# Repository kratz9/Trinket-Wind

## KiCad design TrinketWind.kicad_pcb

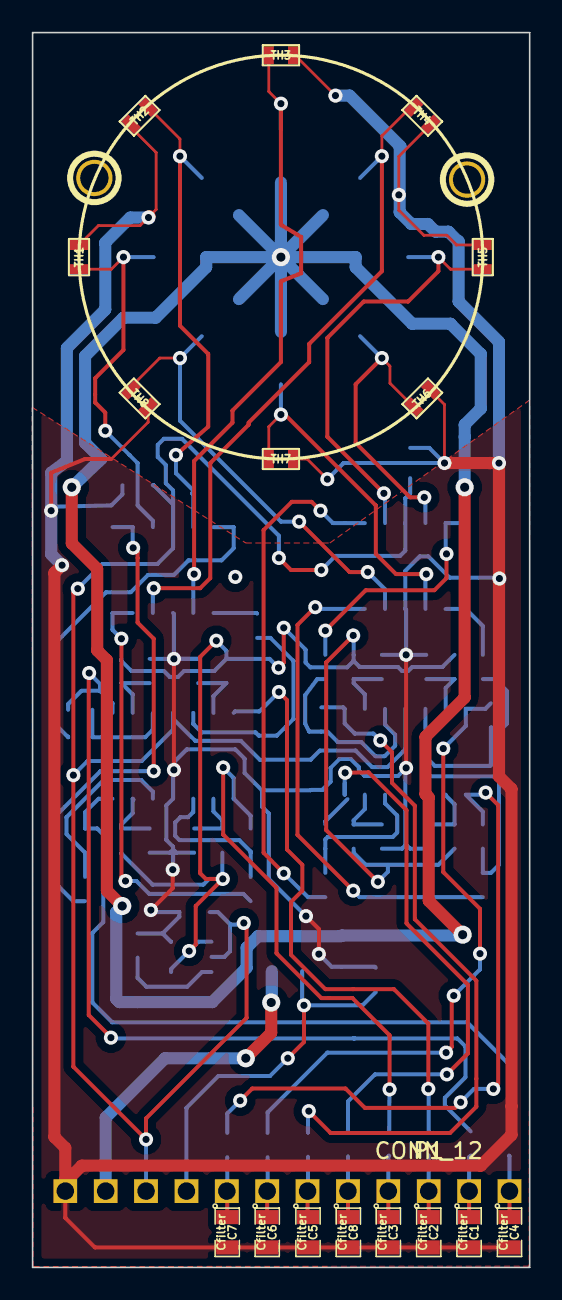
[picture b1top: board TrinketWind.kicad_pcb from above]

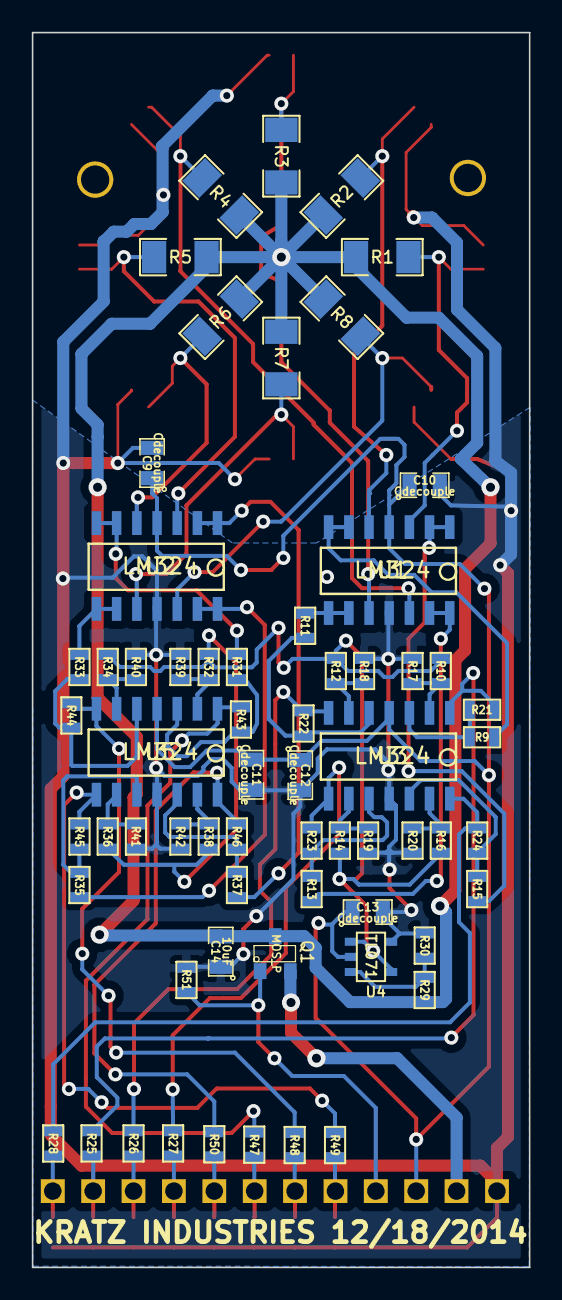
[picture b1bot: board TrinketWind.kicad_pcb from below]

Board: 2 copper layers, 31.3 x 77.7 mm, 82 parts (63 on the bottom side), 55 nets.

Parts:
1PIN, 1PIN#2: P***; 1pin
C1, C2, C3, C4, C5, C6, C7, C8: Cfilter; SM0805
C9, C10, C11, C12, C13: Cdecouple; SM0805
C14: 10uF; SM0805
P1: CONN_12; 12_PIN_HEADER
Q1: MOS_P; SOT23
R1, R2, R3, R4, R5, R6, R7, R8: RD; SM1206
R9, R10, R11, R12, R13, R14, R15, R16, R31, R32, R33, R34, R35, R36, R37, R38: OpR1; SM0603
R17, R18, R19, R20, R21, R22, R23, R24, R39, R40, R41, R42, R43, R44, R45, R46: OpR2; SM0603
R25, R26, R27, R28, R47, R48, R49, R50: Rfilter; SM0603
R29: FloorRef1; SM0603
R30: FloorRef2; SM0603
R51: 10K; SM0603
TH1, TH2, TH3, TH4, TH5, TH6, TH7, TH8: THERM; SM0603
U1, U2, U3, U5: LM324; SOIC_14_QUAD_OPAMP
U4: TL071; SOT23-5

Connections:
ARef: C14.2, Q1.3D, R1.1, R2.1, R3.1, R4.1, R5.1, R6.1, R7.1, R8.1, R29.1
Control: P1.9, Q1.1G, R51.1
GND: C1.2, C2.2, C3.2, C4.2, C5.2, C6.2, C7.2, C8.2, C9.2, C10.2, C11.2, C12.2, C13.2, C14.1, P1.12, R17.1, R18.1, R19.1, R20.1, R30.2, R39.1, R40.1, R41.1, R42.1, R51.2, TH1.2, TH2.2, TH3.2, TH4.2, TH5.2, TH6.2, TH7.2, TH8.2, U1.11, U2.11, U3.11, U4.5, U5.11
unnamed: R23.1, R27.2, U3.8
unnamed: R13.1, R23.2, U3.10
unnamed: R11.1, R22.2, U3.5
unnamed: R22.1, R26.2, U3.7
unnamed: R12.1, R18.2, U3.6
unnamed: R37.1, R46.2, U5.12
unnamed: R46.1, R50.2, U5.14
unnamed: R14.1, R19.2, U3.9
unnamed: R9.1, R21.2, U3.3
unnamed: R21.1, R25.2, U3.1
unnamed: R16.1, R20.2, U3.13
unnamed: R29.2, R30.1, U4.3
unnamed: R10.1, R17.2, U3.2
unnamed: R35.1, R45.2, U5.10
unnamed: R45.1, R49.2, U5.8
unnamed: R36.1, R41.2, U5.9
unnamed: R34.1, R40.2, U5.6
unnamed: R31.1, R43.2, U5.3
unnamed: R43.1, R47.2, U5.1
unnamed: R38.1, R42.2, U5.13
unnamed: R32.1, R39.2, U5.2
unnamed: R33.1, R44.2, U5.5
unnamed: R44.1, R48.2, U5.7
unnamed: R1.2, TH1.1, U1.3
unnamed: R2.2, TH2.1, U1.5
unnamed: R3.2, TH3.1, U1.10
unnamed: R24.1, R28.2, U3.14
unnamed: R15.1, R24.2, U3.12
unnamed: R7.2, TH7.1, U2.10
unnamed: R8.2, TH8.1, U2.12
unnamed: R4.2, TH4.1, U1.12
unnamed: R5.2, TH5.1, U2.3
unnamed: R6.2, TH6.1, U2.5
Out1: C4.1, P1.1, R28.1
Out2: C1.1, P1.2, R25.1
Out3: C2.1, P1.3, R26.1
Out4: C3.1, P1.4, R27.1
Out5: C8.1, P1.5, R50.1
Out6: C5.1, P1.6, R47.1
Out7: C6.1, P1.7, R48.1
Out8: C7.1, P1.8, R49.1
Sense1: R15.2, U1.1, U1.2
Sense2: R9.2, U1.6, U1.7
Sense3: R11.2, U1.8, U1.9
Sense4: R13.2, U1.13, U1.14
Sense5: R37.2, U2.1, U2.2
Sense6: R31.2, U2.6, U2.7
Sense7: R33.2, U2.8, U2.9
Sense8: R35.2, U2.13, U2.14
Vcc: C9.1, C10.1, C11.1, C12.1, C13.1, P1.10, U1.4, U2.4, U3.4, U4.2, U5.4
Vmin: R10.2, R12.2, R14.2, R16.2, R32.2, R34.2, R36.2, R38.2, U4.1, U4.4
Vpower: P1.11, Q1.2S

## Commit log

2014-12-03 :boom::camel: Added .gitattributes & .gitignore files
2014-12-03 Basic Sensor Schematic
2014-12-08 Schematic and component value worksheet
2014-12-08 Update With Schematic PDF
2014-12-16 Layout Partial
    Schematic Finished and Layout partially done
2014-12-17 Updates
    Closer to final layout
2014-12-18 12-17-14
2014-12-18 Final?
2014-12-19 Fixed calculation sheet
    Adjusted component calc sheet to adjust for buffer amps
2014-12-20 Value Calculations
2014-12-24 Start of Coding
2014-12-27 Code
2015-01-02 Code updates
2015-01-03 Experimental Code
